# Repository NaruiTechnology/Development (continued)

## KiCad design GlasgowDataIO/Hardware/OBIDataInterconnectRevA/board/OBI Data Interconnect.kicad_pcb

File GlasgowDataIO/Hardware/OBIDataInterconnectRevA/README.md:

# OBI Data Interconnect Rev A

Redesigned companion interconnect for the Glasgow Interface Explorer rev C3 and the OBI scan subtarget. This board is passive: it carries the Glasgow expansion signals to three 2x10 field headers and provides mutually exclusive Glasgow/external 3.3 V selection.

The electrical baseline is the KiCad 9 source from `/home/vboxuser/Downloads/rawData/硬件文档/OBI Data Interconnect.kicad_pcb`. The board keeps the proven connector, resistor-array, jumper, capacitor, and mounting hardware population. The redesign makes the shared-bus contract explicit on the board and in the release documentation:

- J3: D-1 through D-8
- J4: D-9 through D-16
- J2: D-17 through D-24
- D-1 through D-14 are the active 14-bit ADC/DAC bus for the scan subtarget; D-15 through D-24 remain reserved.
- Glasgow `+3.3V` and external `+3.3V` are selected by JP1/JP2; both jumpers must never be fitted together.
- GNDD is the digital return used by this interconnect. It is not silently merged with the analog return on the scan board.

## Source

- `board/OBI Data Interconnect.kicad_pcb`
- `board/OBI Data Interconnect.kicad_sch`
- `board/OBI Data Interconnect.kicad_pro`
- `board/OBI Data Interconnect.pretty/`
- `board/Scan Generator.pretty/`
- `board/3D Models/`

## Companion contract

See [SHARED_BUS_CONTRACT.md](../ScanSubtargetRevA/SHARED_BUS_CONTRACT.md) and [PINOUT.md](PINOUT.md). The interconnect does not perform ADC/DAC arbitration; the Glasgow applet owns the cycle timing. The board only preserves the one-bus physical mapping and supplies controlled connector/power access.

## Release caveat

The source is KiCad 9 format. The container currently has KiCad 8 CLI, which cannot parse this source. Therefore the package includes the complete source and audit evidence, but the revised board has not been fabrication-cleared by a local KiCad 9 DRC/ERC run in this session. Run KiCad 9 DRC/ERC and regenerate Gerbers, drill, position, STEP, and IPC-2581 before ordering.

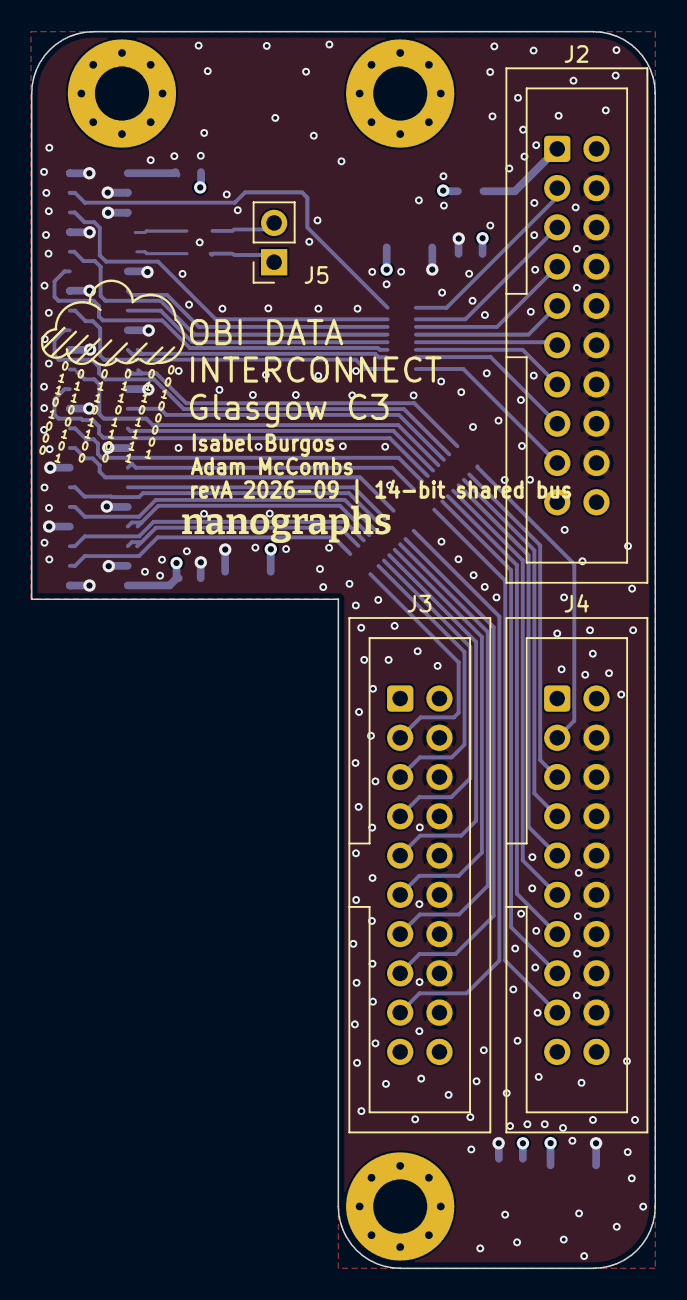
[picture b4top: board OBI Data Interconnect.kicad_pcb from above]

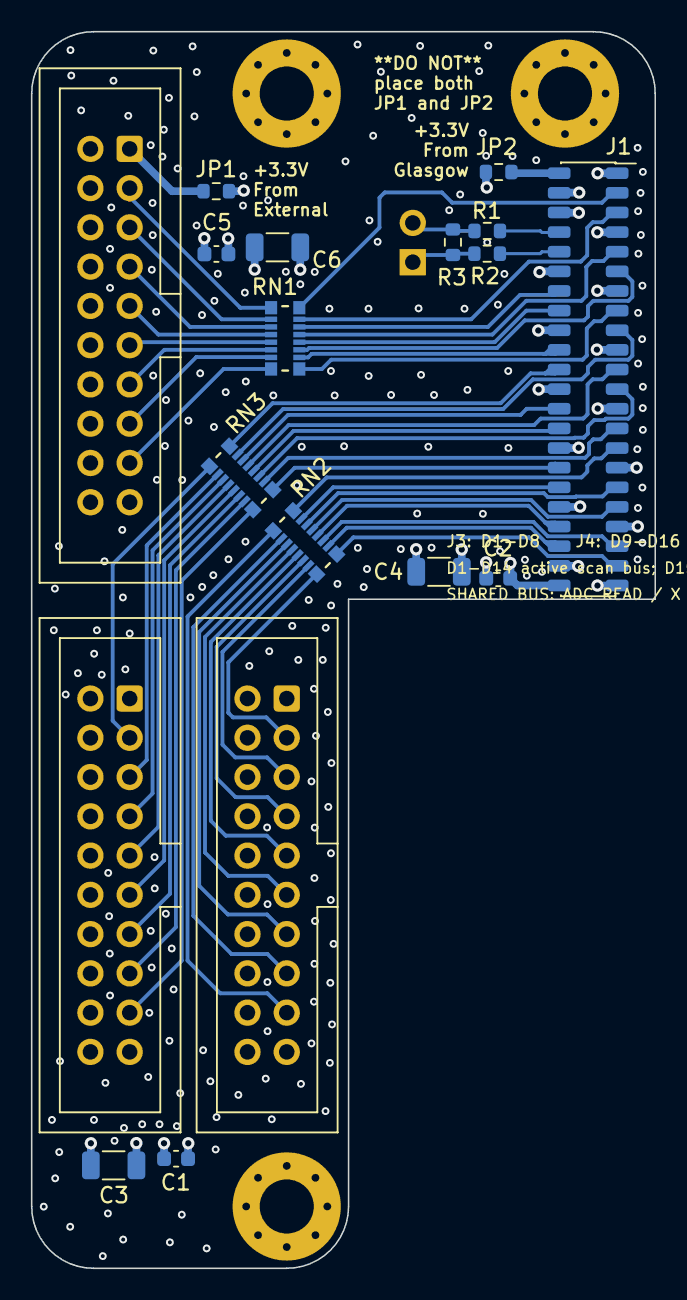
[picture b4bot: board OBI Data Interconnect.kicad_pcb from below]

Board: 4 copper layers, 40.3 x 80.0 mm, 22 parts (15 on the bottom side), 56 nets.

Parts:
C1, C2, C5: 0.1uF; C_0603_1608Metric
C3, C4, C6: 4.7uF; C_1206_3216Metric
H1, H2, H3: MountingHole; MountingHole_3.5mm_Pad_Via_CrtYd
J1: Conn_02x22_Odd_Even; PinReceptacle_2x22_P1.27mm_Vertical_BackSide_SMD
J2, J3, J4: Conn_02x10_Odd_Even; IDC-Header_Receptacle_2x10_P2.54mm_Vertical_No_Pin_1_Mark
J5: Conn_01x02_Pin; PinSocket_1x02_P2.54mm_Vertical
JP1, JP2: Jumper_2_Open; R_0603_1608Metric
R1, R2, R3: R; R_0603_1608Metric
RN1, RN2, RN3: R_Pack08; RES_EXB2HV

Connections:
+3.3V: C1.1, C2.1, C3.1, C4.1, C5.1, C6.1, J1.44, J2.2, J3.2, J4.2, JP1.1 (A), JP2.1 (A)
/B1: J1.39, RN2.3 (R3.1)
/B2: J1.41, RN2.1 (R1.1)
/C1: J1.33, RN2.6 (R6.1)
/C2: J1.35, RN2.5 (R5.1)
/C3: J1.38, RN2.4 (R4.1)
/C4: J1.40, RN2.2 (R2.1)
/D1: J1.29, RN2.8 (R8.1)
/D2: J1.32, RN3.9 (R8.2)
/D3: J1.34, RN2.7 (R7.1)
/D-1: J3.3, RN2.16 (R1.2)
/D-2: J3.5, RN2.15 (R2.2)
/D-3: J3.7, RN2.14 (R3.2)
/D-4: J3.9, RN2.13 (R4.2)
/D-5: J3.11, RN2.12 (R5.2)
/D-6: J3.13, RN2.11 (R6.2)
/D-7: J3.15, RN2.10 (R7.2)
/D-8: J3.17, RN2.9 (R8.2)
/D-9: J4.3, RN3.1 (R1.1)
/D-10: J4.5, RN3.2 (R2.1)
/D-11: J4.7, RN3.3 (R3.1)
/D-12: J4.9, RN3.4 (R4.1)
/D-13: J4.11, RN3.5 (R5.1)
/D-14: J4.13, RN3.6 (R6.1)
/D-15: J4.15, RN3.7 (R7.1)
/D-16: J4.17, RN3.8 (R8.1)
/D-17: J2.3, RN1.1 (R1.1)
/D-18: J2.5, RN1.2 (R2.1)
/D-19: J2.7, RN1.3 (R3.1)
/D-20: J2.9, RN1.4 (R4.1)
/D-21: J2.11, RN1.5 (R5.1)
/D-22: J2.13, RN1.6 (R6.1)
/D-23: J2.15, RN1.7 (R7.1)
/D-24: J2.17, RN1.8 (R8.1)
/E1: J1.27, RN3.10 (R7.2)
/E2: J1.28, RN3.12 (R5.2)
/E3: J1.26, RN3.14 (R3.2)
/F1: J1.21, RN3.13 (R4.2)
/F2: J1.23, RN3.11 (R6.2)
/F3: J1.20, RN1.10 (R7.2)
/F4: J1.22, RN3.16 (R1.2)
/G1: J1.15, RN1.9 (R8.2)
/G2: J1.17, RN3.15 (R2.2)
/G3: J1.16, RN1.12 (R5.2)
/H1: J1.9, RN1.13 (R4.2)
/H2: J1.11, RN1.11 (R6.2)
/H3: J1.14, RN1.14 (R3.2)
/J1: J1.5, RN1.15 (R2.2)
/K1: J1.3, RN1.16 (R1.2)
/Z12_N: J1.10, R2.1
/Z12_P: J1.8, R1.1
External +3.3V Source: J2.1, JP1.2 (B)
GNDD: C1.2, C2.2, C3.2, C4.2, C5.2, C6.2, J1.1, J1.4, J1.6, J1.7, J1.12, J1.13, J1.18, J1.19, J1.24, J1.25, J1.30, J1.31, J1.36, J1.37, J1.42, J1.43, J2.4, J2.6, J2.8, J2.10, J2.12, J2.14, J2.16, J2.18, J3.4, J3.6, J3.8, J3.10, J3.12, J3.14, J3.16, J3.18, J4.4, J4.6, J4.8, J4.10, J4.12, J4.14, J4.16, J4.18
Glasgow +3.3V Source: J1.2, JP2.2 (B)
unnamed: J5.1, R2.2, R3.1
unnamed: J5.2, R1.2, R3.2

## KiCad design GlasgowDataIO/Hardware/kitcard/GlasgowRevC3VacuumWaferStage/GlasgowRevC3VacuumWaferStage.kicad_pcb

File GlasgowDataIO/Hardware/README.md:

# Hardware workspace

The active scan/acquisition redesign starts at
[ScanAcquisitionV2](ScanAcquisitionV2/README.md). It is a new architecture with
independent ADC and DAC data paths, started on 2026-09-10. Component selection,
schematic and layout are not yet complete.

| Location | Purpose |
| --- | --- |
| `ScanAcquisitionV2/` | Active scan/acquisition design from a fresh requirements baseline |
| `archive/obi-shared-bus-20260910/` | Preserved OBI-derived scan/interconnect source, libraries, evidence and manufacturing packages |
| `kitcard/` | Existing motion/stage-control projects; outside this redesign |

The old top-level `ScanSubtargetRevA`, `OBIDataInterconnectRevA`, and `tools`
directories moved together into the dated archive. Its `MANIFEST.json` records
SHA256 and size for all 307 original files; every file was checked after moving.
No old PCB copper, schematic circuitry, BOM, footprints, pinout, or fabrication
exports have been copied into the active project. Retained archive documents
are historical; their prior release claims do not apply to the new design.

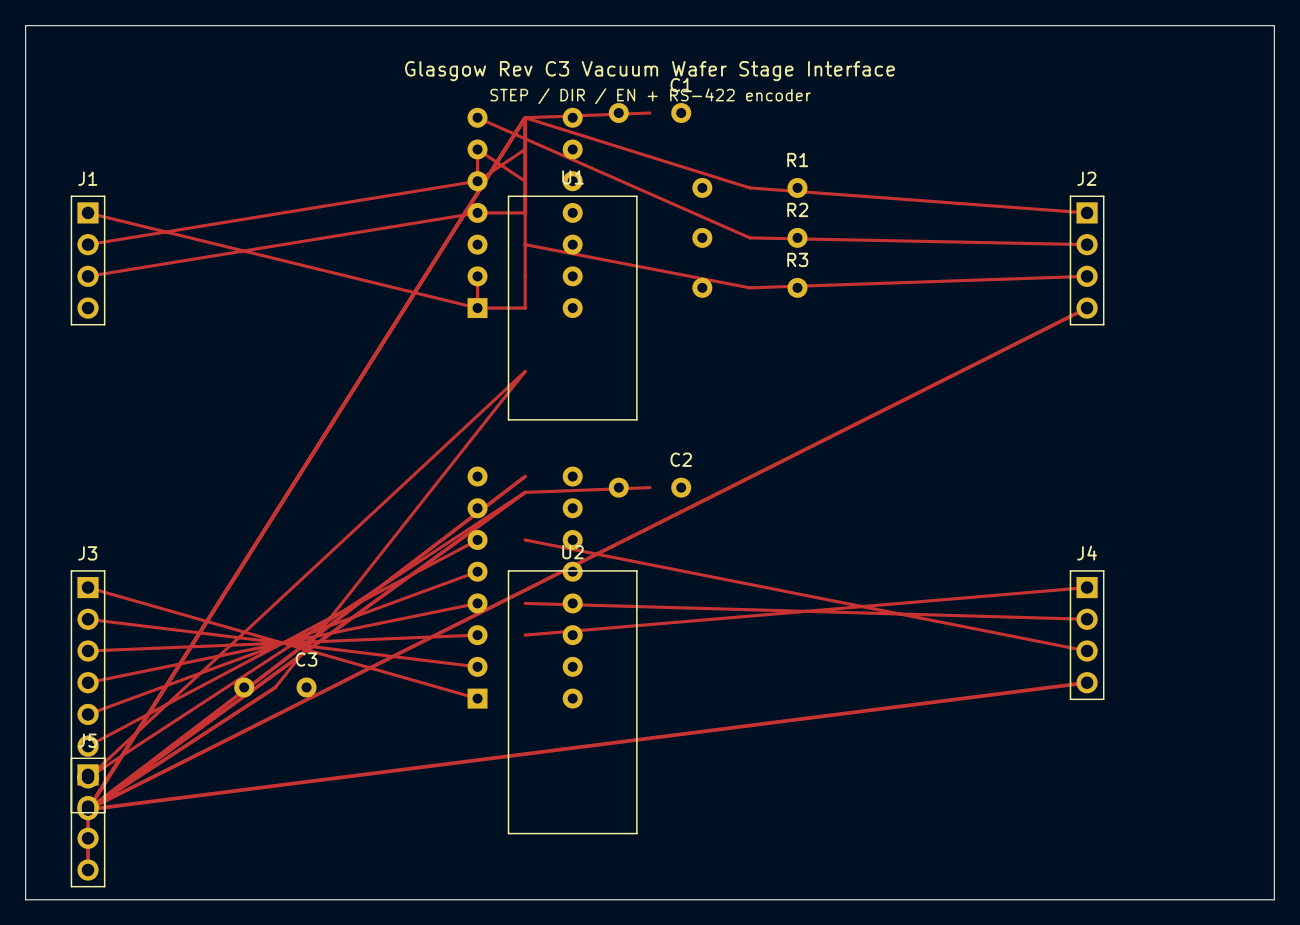
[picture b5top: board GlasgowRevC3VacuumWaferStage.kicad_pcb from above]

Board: 2 copper layers, 100.0 x 70.0 mm, 13 parts (0 on the bottom side), 23 nets.

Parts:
C1, C2: 100nF; C_Disc_D5.0mm_W2.5mm_P5.00mm
C3: 10uF; C_Disc_D5.0mm_W2.5mm_P5.00mm
J1: GLASGOW_IN; PinHeader_1x04_P2.54mm_Vertical
J2: DRIVER_OUT; PinHeader_1x04_P2.54mm_Vertical
J3: ENCODER_IN; PinHeader_1x08_P2.54mm_Vertical
J4: ENCODER_OUT; PinHeader_1x04_P2.54mm_Vertical
J5: INTERLOCK; PinHeader_1x04_P2.54mm_Vertical
R1, R2, R3: 100R; R_Axial_DIN0207_L6.3mm_D2.5mm_P7.62mm_Horizontal
U1: 74HCT14; DIP-14_W7.62mm
U2: AM26LS32; DIP-16_W7.62mm

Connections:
+5V_ENC: C1.1, C2.1, C3.1, J3.7, U1.14, U2.13, U2.14, U2.15, U2.16
DIR_DRIVER: J2.2, R2.2
DIR_GLASGOW: J1.2, U1.5
DIR_MID: U1.6, U1.9
DIR_OUT: R2.1, U1.8
ENC_A: J4.1, U2.3
ENC_A_N: J3.2, U2.2
ENC_A_P: J3.1, U2.1
ENC_B: J4.2, U2.6
ENC_B_N: J3.4, U2.5
ENC_B_P: J3.3, U2.4
ENC_Z: J4.3, U2.7, U2.11
ENC_Z_N: J3.6, U2.10
ENC_Z_P: J3.5, U2.9
EN_DRIVER: J2.3, R3.2
EN_GLASGOW: J1.3, U1.11
EN_MID: U1.10, U1.13
EN_OUT: R3.1, U1.12
GND: C1.2, C2.2, C3.2, J1.4, J2.4, J3.8, J4.4, J5.4, U1.7, U2.8, U2.12
STEP_DRIVER: J2.1, R1.2
STEP_GLASGOW: J1.1, U1.1
STEP_MID: U1.2, U1.3
STEP_OUT: R1.1, U1.4

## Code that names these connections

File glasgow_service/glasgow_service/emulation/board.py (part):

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* G5LE relay operate (10 ms) / release (5 ms) times;
* U9/U10 ADS1115 @0x48/0x49 behind the 68k/22k divider, 100 nF anti-alias
  filter and BAT54S clamp; ALERT/RDY wired-AND to GPIO23;
* rail status optos (ESTOP_OK_N GPIO5, SAFE_OK_N GPIO6, low = OK);
* RS-485 (MAX3485, DE/RE on GPIO18, half duplex) and RS-232 (MAX3232);
* the indicator LEDs.
"""
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        return items

    def _u3_pins(self) -> int:
        """DI_N1..16 at the U3 pins: opto on pulls low, else R12x pull-up."""
        if not self.pi.rail_3v3:
            return 0
        word = 0
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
